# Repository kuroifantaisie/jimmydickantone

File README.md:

# jimmydickantone
My public portfolio

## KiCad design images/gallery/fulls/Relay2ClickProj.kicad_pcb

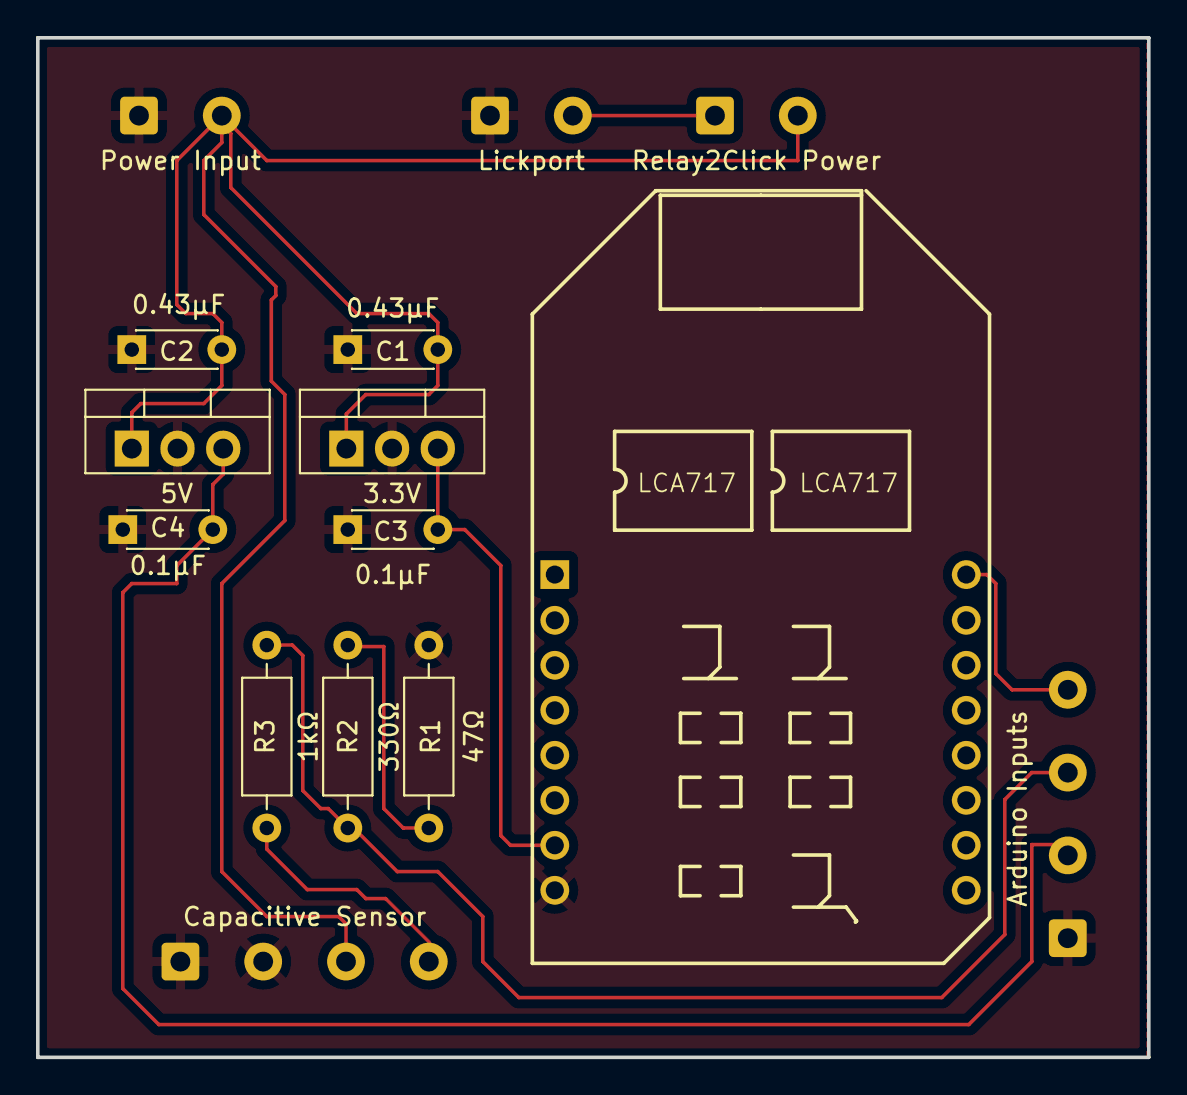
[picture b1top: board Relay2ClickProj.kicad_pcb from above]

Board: 2 copper layers, 61.7 x 56.6 mm, 15 parts (0 on the bottom side), 9 nets.

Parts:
BT1: Power Input; SolderWire-0.5sqmm_1x02_P4.6mm_D0.9mm_OD2.1mm
C1, C2: 0.43µF; C_Disc_D4.3mm_W1.9mm_P5.00mm
C3, C4: 0.1µF; C_Disc_D4.3mm_W1.9mm_P5.00mm
J1: Capacitive Sensor; SolderWire-0.5sqmm_1x04_P4.6mm_D0.9mm_OD2.1mm
J2: Relay2Click Power; SolderWire-0.5sqmm_1x02_P4.6mm_D0.9mm_OD2.1mm
J3: Arduino Inputs; SolderWire-0.5sqmm_1x04_P4.6mm_D0.9mm_OD2.1mm
J4: Lickport; SolderWire-0.5sqmm_1x02_P4.6mm_D0.9mm_OD2.1mm
K1: Relay2Click
R1: 47Ω; R_Axial_DIN0207_L6.3mm_D2.5mm_P10.16mm_Horizontal
R2: 330Ω; R_Axial_DIN0207_L6.3mm_D2.5mm_P10.16mm_Horizontal
R3: 1kΩ; R_Axial_DIN0207_L6.3mm_D2.5mm_P10.16mm_Horizontal
U1: 3.3V; TO-220-3_Vertical
U2: 5V; TO-220-3_Vertical

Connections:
GND: BT1.1 (-), C1.1, C2.1, C3.1, C4.1, J1.1, J1.2, J3.1, J4.1, K1.8 (GND), R1.1, U1.2 (GND), U2.2 (GND)
unnamed: BT1.2 (+), C1.2, C2.2, J1.3, J2.2 (Pin_1), U1.1 (IN), U2.1 (IN)
unnamed: J1.4, R3.1
unnamed: J2.1 (Pin_2), J4.2
unnamed: C4.2, J3.2, U2.3 (OUT)
unnamed: J3.3, R2.2, R3.2
unnamed: J3.4, K1.16 (RL1)
unnamed: C3.2, K1.7 (3.3V), U1.3 (OUT)
unnamed: R1.2, R2.1

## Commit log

2024-12-16 Rename testjim.my.canva.site.html to index.html
2024-12-19 Rename annotated-416 20Homework 207-1.html to hopfieldnetwork
2024-12-19 Rename hopfieldnetwork to hopfieldnetwork.html
